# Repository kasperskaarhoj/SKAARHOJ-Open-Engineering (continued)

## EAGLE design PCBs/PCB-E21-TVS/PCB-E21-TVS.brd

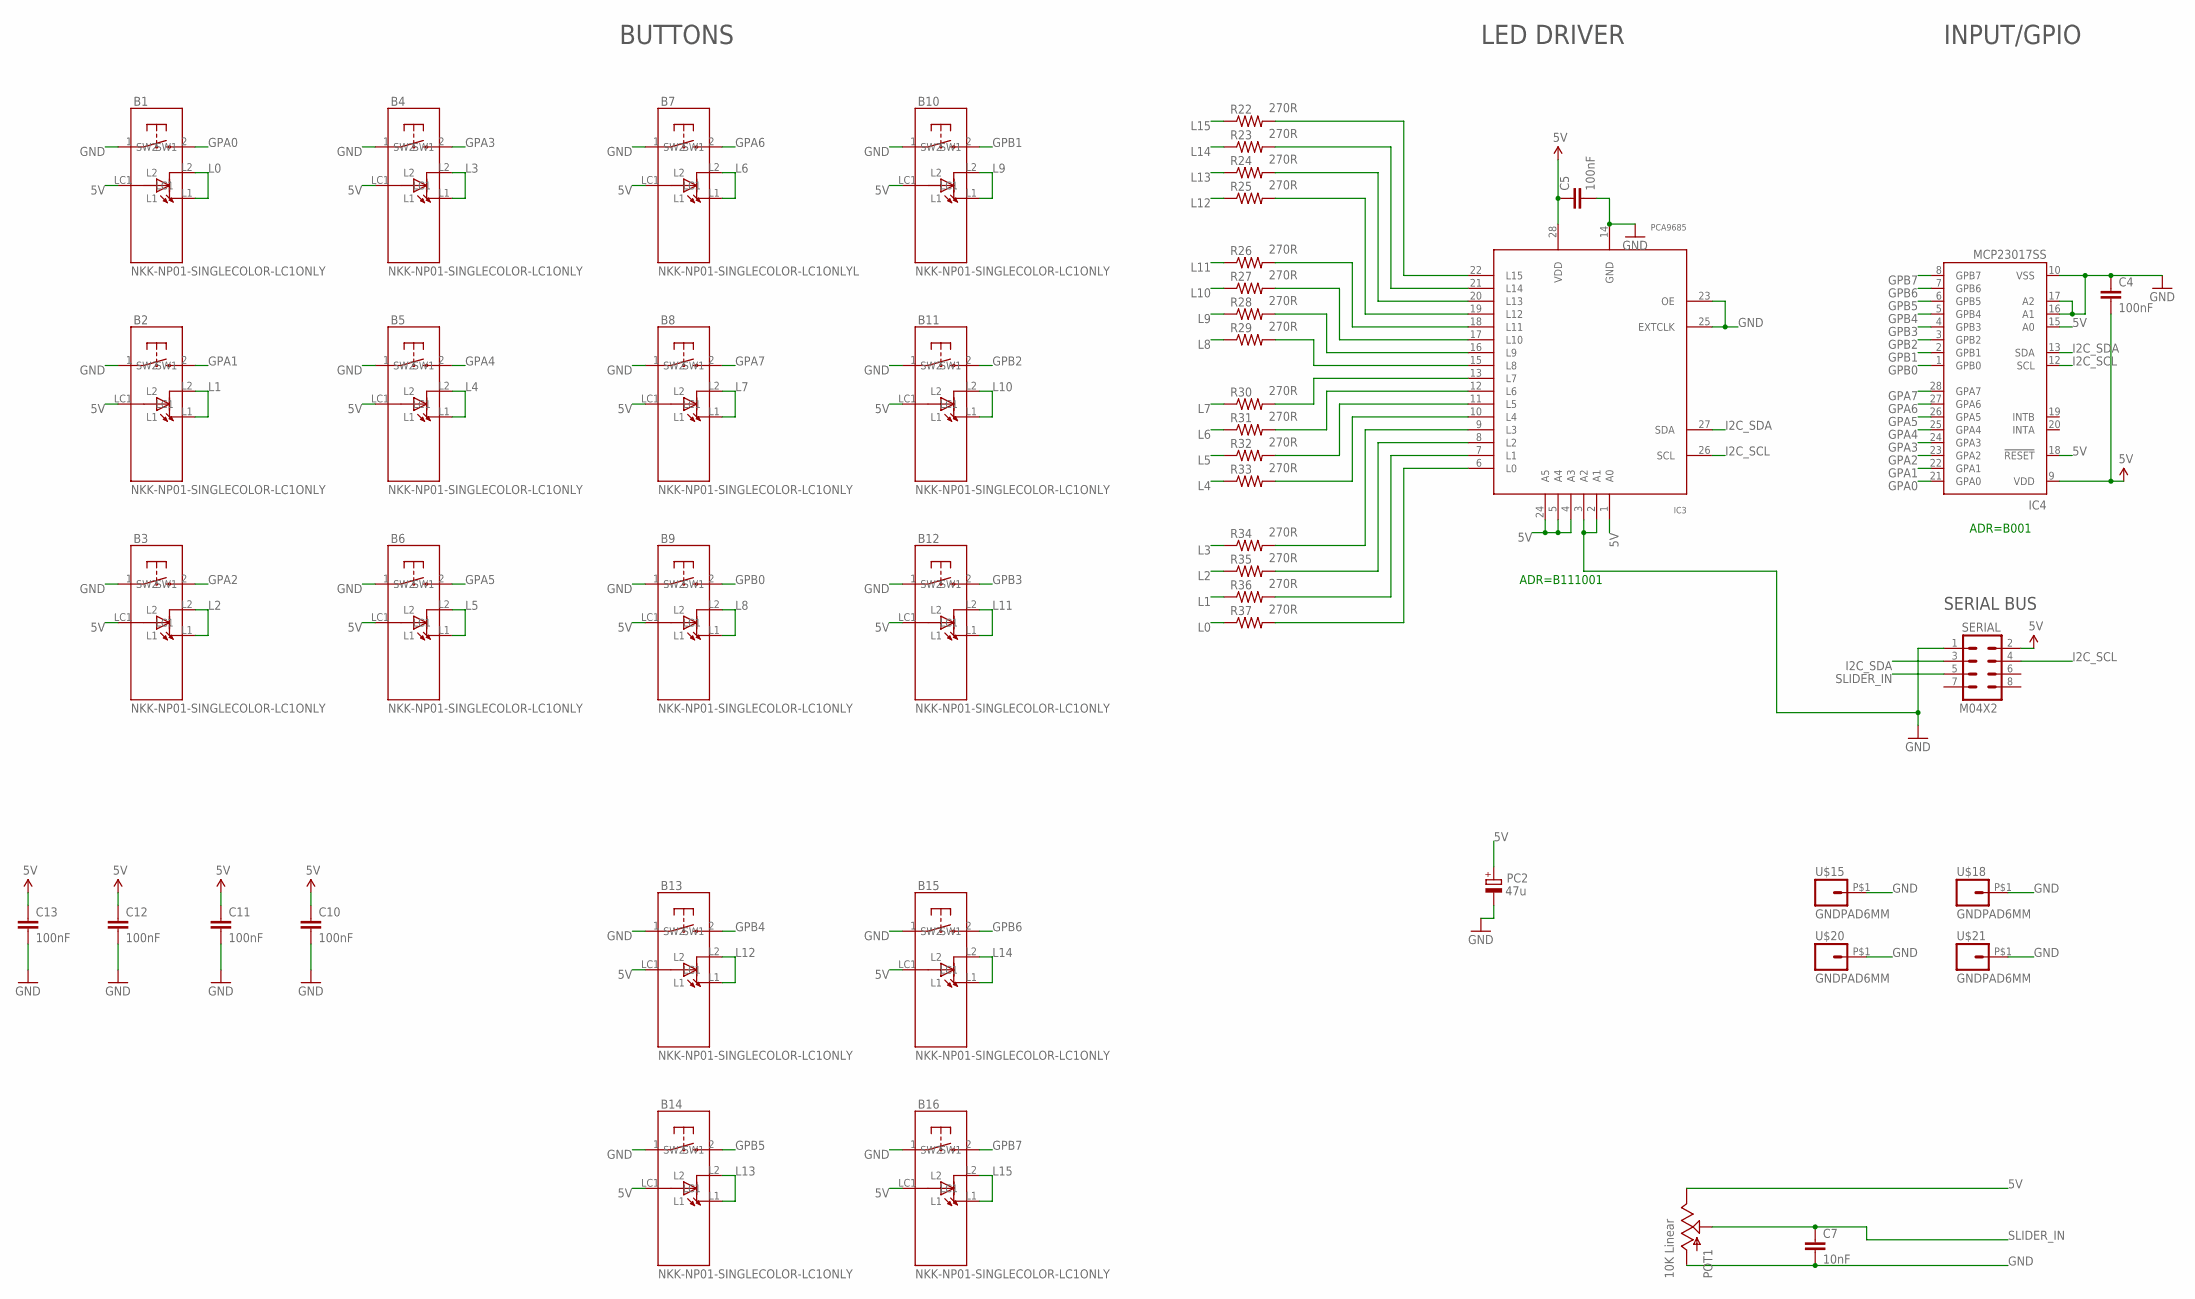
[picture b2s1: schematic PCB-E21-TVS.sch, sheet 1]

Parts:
B1, B2, B3, B4, B5, B6, B8, B9, B10, B11, B12, B13, B14, B15, B16: NKK-NP01-SINGLECOLOR-LC1ONLY; NKK-NP01_LESSHOLES2
B7: NKK-NP01-SINGLECOLOR-LC1ONLYL; NKK-NP01_LESSHOLES3
C4, C5, C10, C11, C12, C13: 100nF; 0603-CAP
C7: 10nF; 0603-CAP
IC3: PCA9685; TSSOP28
IC4: MCP23017SS; SSOP28; MPN MCP23017-E/SS
PC2: 47u; PANASONIC_D
POT1: 10K Linear; SLIDER20-CAR2
R22, R23, R24, R25, R26, R27, R28, R29, R30, R31, R32, R33, R34, R35, R36, R37: 270R; 0603-RES
SERIAL: M04X2; 2X4
U$15, U$18, U$20, U$21: GNDPAD6MM; 3.2MMPAD6MM

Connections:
5V: B1.LC1, B2.LC1, B3.LC1, B4.LC1, B5.LC1, B6.LC1, B7.LC1, B8.LC1, B9.LC1, B10.LC1, B11.LC1, B12.LC1, B13.LC1, B14.LC1, B15.LC1, B16.LC1, C4.2, C5.1, C10.1, C11.1, C12.1, C13.1, IC3.1 (A0), IC3.4 (A3), IC3.5 (A4), IC3.24 (A5), IC3.28 (VDD), IC4.9 (VDD), IC4.15 (A0), IC4.18 (!RESET), PC2.+, POT1.1 (E), SERIAL.2
GND: B1.1 (SW1), B2.1 (SW1), B3.1 (SW1), B4.1 (SW1), B5.1 (SW1), B6.1 (SW1), B7.1 (SW1), B8.1 (SW1), B9.1 (SW1), B10.1 (SW1), B11.1 (SW1), B12.1 (SW1), B13.1 (SW1), B14.1 (SW1), B15.1 (SW1), B16.1 (SW1), C4.1, C5.2, C7.2, C10.2, C11.2, C12.2, C13.2, IC3.2 (A1), IC3.3 (A2), IC3.14 (GND), IC3.23 (OE), IC3.25 (EXTCLK), IC4.10 (VSS), IC4.16 (A1), IC4.17 (A2), PC2.-, POT1.3 (A), SERIAL.1, U$15.P$1, U$18.P$1, U$20.P$1, U$21.P$1
GPA0: B1.2 (SW2), IC4.21 (GPA0)
GPA1: B2.2 (SW2), IC4.22 (GPA1)
GPA2: B3.2 (SW2), IC4.23 (GPA2)
GPA3: B4.2 (SW2), IC4.24 (GPA3)
GPA4: B5.2 (SW2), IC4.25 (GPA4)
GPA5: B6.2 (SW2), IC4.26 (GPA5)
GPA6: B7.2 (SW2), IC4.27 (GPA6)
GPA7: B8.2 (SW2), IC4.28 (GPA7)
GPB0: B9.2 (SW2), IC4.1 (GPB0)
GPB1: B10.2 (SW2), IC4.2 (GPB1)
GPB2: B11.2 (SW2), IC4.3 (GPB2)
GPB3: B12.2 (SW2), IC4.4 (GPB3)
GPB4: B13.2 (SW2), IC4.5 (GPB4)
GPB5: B14.2 (SW2), IC4.6 (GPB5)
GPB6: B15.2 (SW2), IC4.7 (GPB6)
GPB7: B16.2 (SW2), IC4.8 (GPB7)
I2C_SCL: IC3.26 (SCL), IC4.12 (SCL), SERIAL.4
I2C_SDA: IC3.27 (SDA), IC4.13 (SDA), SERIAL.3
L0: B1.L1, B1.L2, R37.1
L1: B2.L1, B2.L2, R36.1
L2: B3.L1, B3.L2, R35.1
L3: B4.L1, B4.L2, R34.1
L4: B5.L1, B5.L2, R33.1
L5: B6.L1, B6.L2, R32.1
L6: B7.L1, B7.L2, R31.1
L7: B8.L1, B8.L2, R30.1
L8: B9.L1, B9.L2, R29.1
L9: B10.L1, B10.L2, R28.1
L10: B11.L1, B11.L2, R27.1
L11: B12.L1, B12.L2, R26.1
L12: B13.L1, B13.L2, R25.1
L13: B14.L1, B14.L2, R24.1
L14: B15.L1, B15.L2, R23.1
L15: B16.L1, B16.L2, R22.1
unnamed: IC3.13 (L7), R30.2
unnamed: IC3.12 (L6), R31.2
unnamed: IC3.11 (L5), R32.2
unnamed: IC3.10 (L4), R33.2
unnamed: IC3.9 (L3), R34.2
unnamed: IC3.8 (L2), R35.2
unnamed: IC3.7 (L1), R36.2
unnamed: IC3.6 (L0), R37.2
unnamed: IC3.15 (L8), R29.2
unnamed: IC3.16 (L9), R28.2
unnamed: IC3.17 (L10), R27.2
unnamed: IC3.18 (L11), R26.2
unnamed: IC3.19 (L12), R25.2
unnamed: IC3.20 (L13), R24.2
unnamed: IC3.21 (L14), R23.2
unnamed: IC3.22 (L15), R22.2
SLIDER_IN: C7.1, POT1.2A (S), SERIAL.5

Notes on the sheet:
ADR=B111001
ADR=B001
BUTTONS
LED DRIVER
INPUT/GPIO
SERIAL BUS

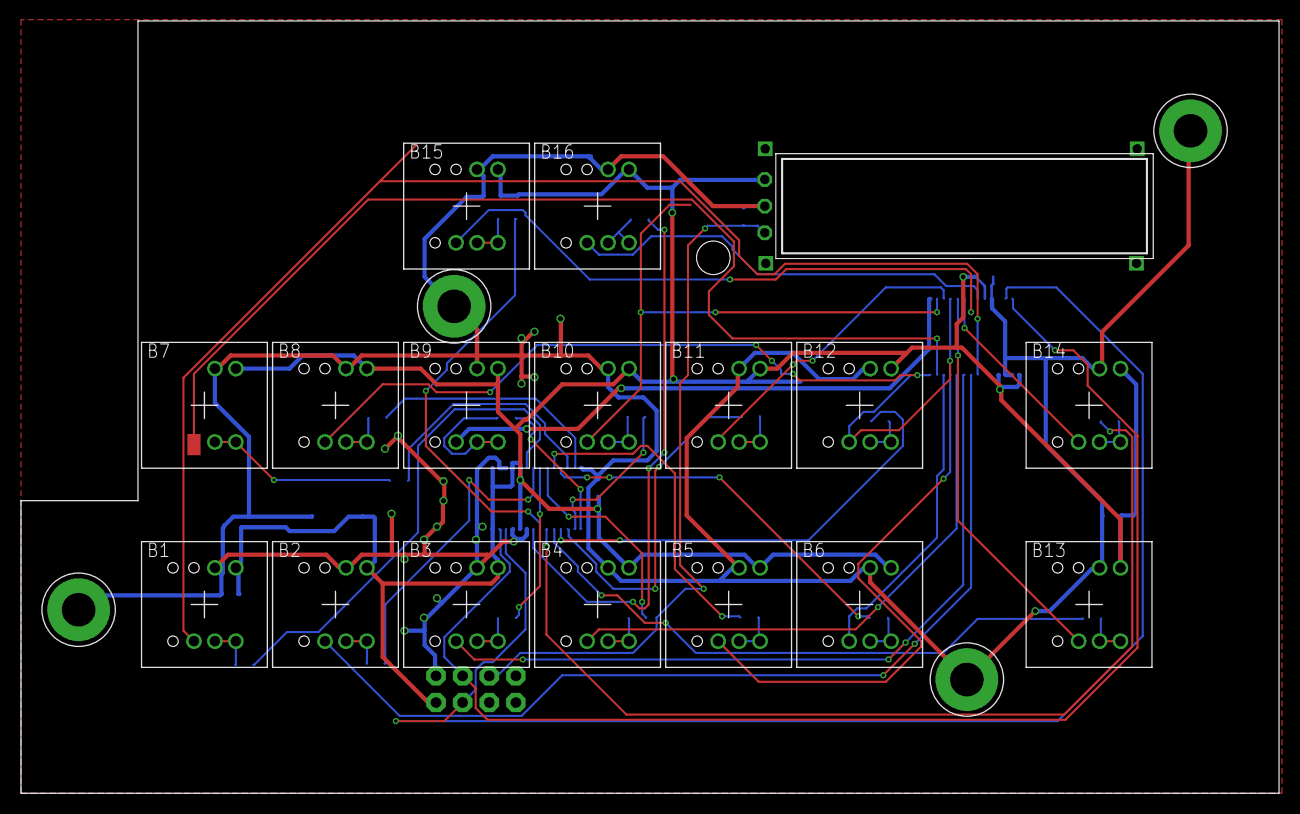
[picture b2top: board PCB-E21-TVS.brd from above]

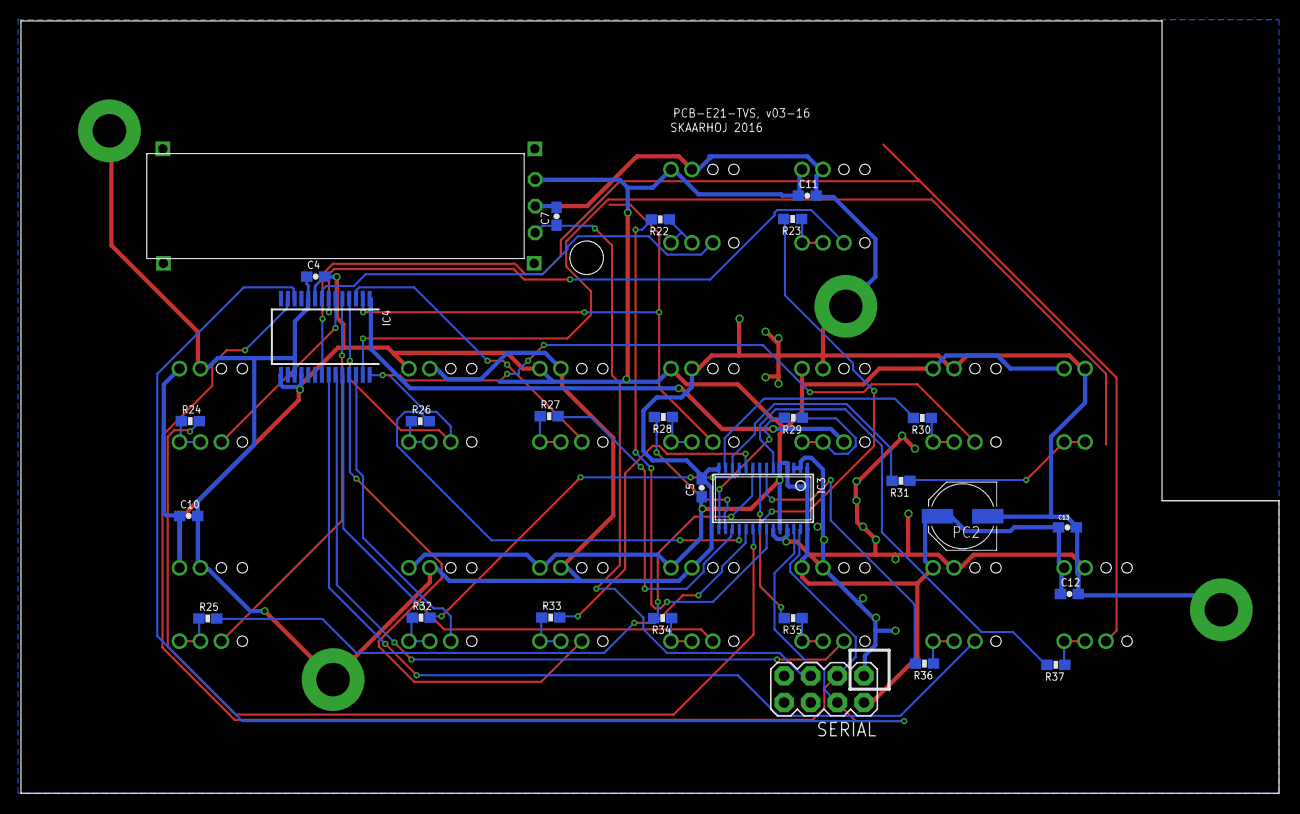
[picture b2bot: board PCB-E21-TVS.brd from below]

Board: 2 copper layers, 120.0 x 73.7 mm, 48 parts (27 on the bottom side), 53 nets.

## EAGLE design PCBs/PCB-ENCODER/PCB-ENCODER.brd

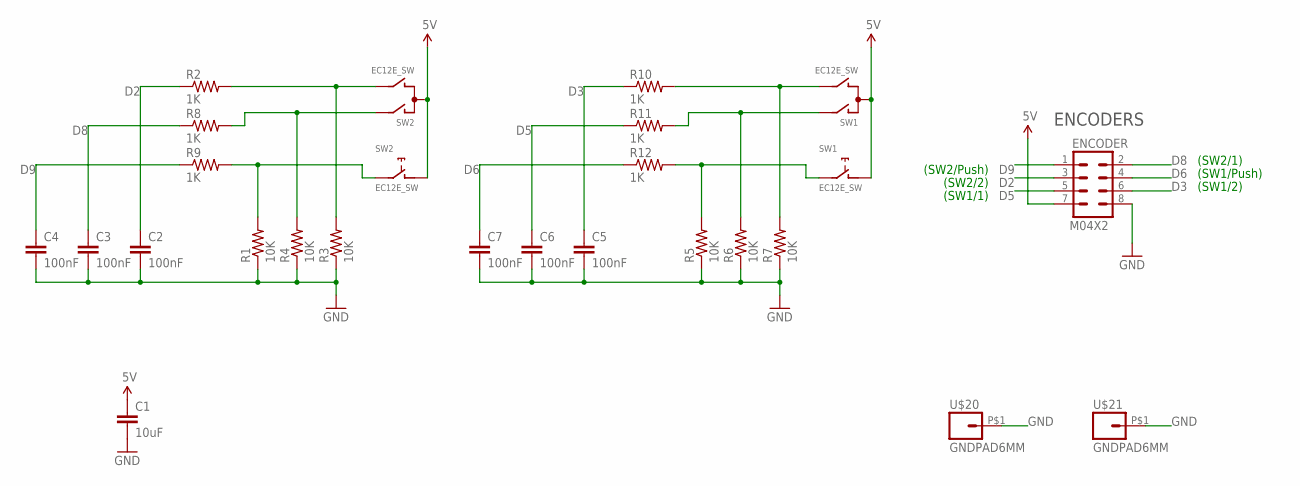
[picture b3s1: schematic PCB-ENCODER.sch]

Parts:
C1: 10uF; 0603-CAP
C2, C3, C4, C5, C6, C7: 100nF; 0603-CAP
ENCODER: M04X2; 2X4
R1, R3, R4, R5, R6, R7: 10K; 0603-RES
R2, R8, R9, R10, R11, R12: 1K; 0603-RES
SW1, SW2: EC12E_SW; ALPS_EC12E_SW
U$20, U$21: GNDPAD6MM; 3.2MMPAD6MM

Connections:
5V: C1.1, ENCODER.7, SW1.C, SW1.D (1), SW2.C, SW2.D (1)
D2: C2.1, ENCODER.3, R2.1
D3: C5.1, ENCODER.6, R10.1
D5: C6.1, ENCODER.5, R11.1
D6: C7.1, ENCODER.4, R12.1
D8: C3.1, ENCODER.2, R8.1
D9: C4.1, ENCODER.1, R9.1
GND: C1.2, C2.2, C3.2, C4.2, C5.2, C6.2, C7.2, ENCODER.8, R1.1, R3.1, R4.1, R5.1, R6.1, R7.1, U$20.P$1, U$21.P$1
unnamed: R2.2, R3.2, SW2.B
unnamed: R7.2, R10.2, SW1.B
unnamed: R6.2, R11.2, SW1.A
unnamed: R4.2, R8.2, SW2.A
unnamed: R1.2, R9.2, SW2.E (2)
unnamed: R5.2, R12.2, SW1.E (2)

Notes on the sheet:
ENCODERS
(SW2/Push)
(SW2/2)
(SW1/1)
(SW2/1)
(SW1/Push)
(SW1/2)

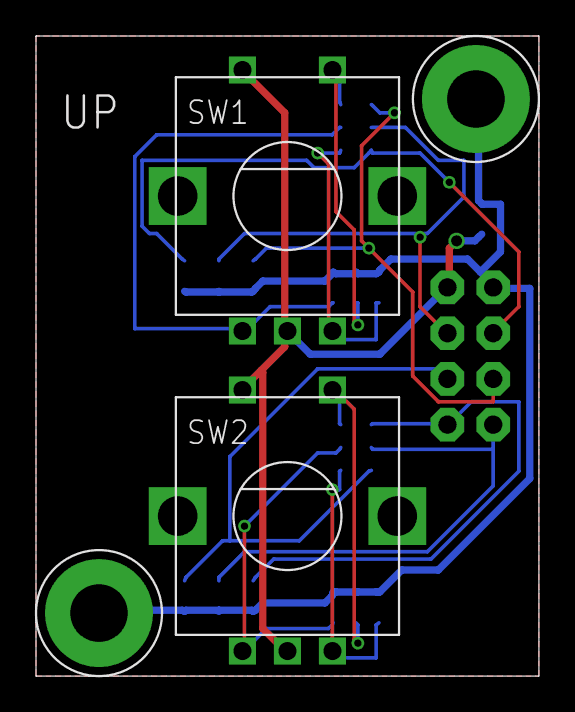
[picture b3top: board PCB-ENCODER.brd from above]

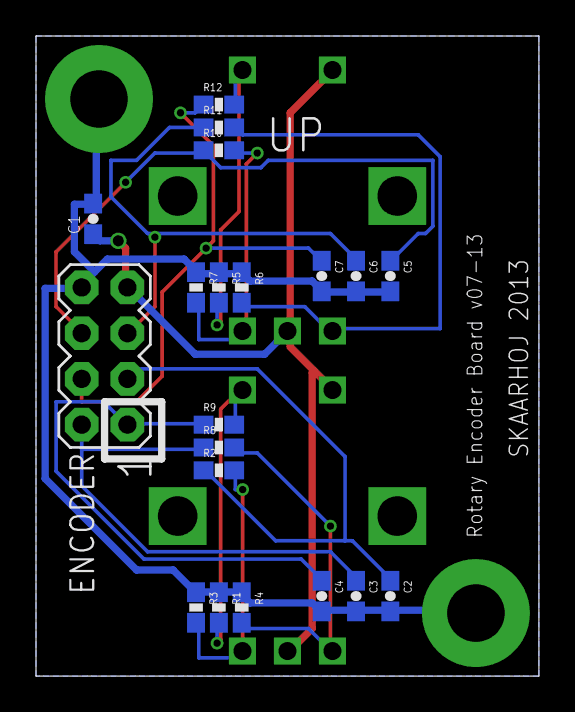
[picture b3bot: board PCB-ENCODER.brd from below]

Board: 2 copper layers, 27.9 x 35.6 mm, 24 parts (20 on the bottom side), 14 nets.

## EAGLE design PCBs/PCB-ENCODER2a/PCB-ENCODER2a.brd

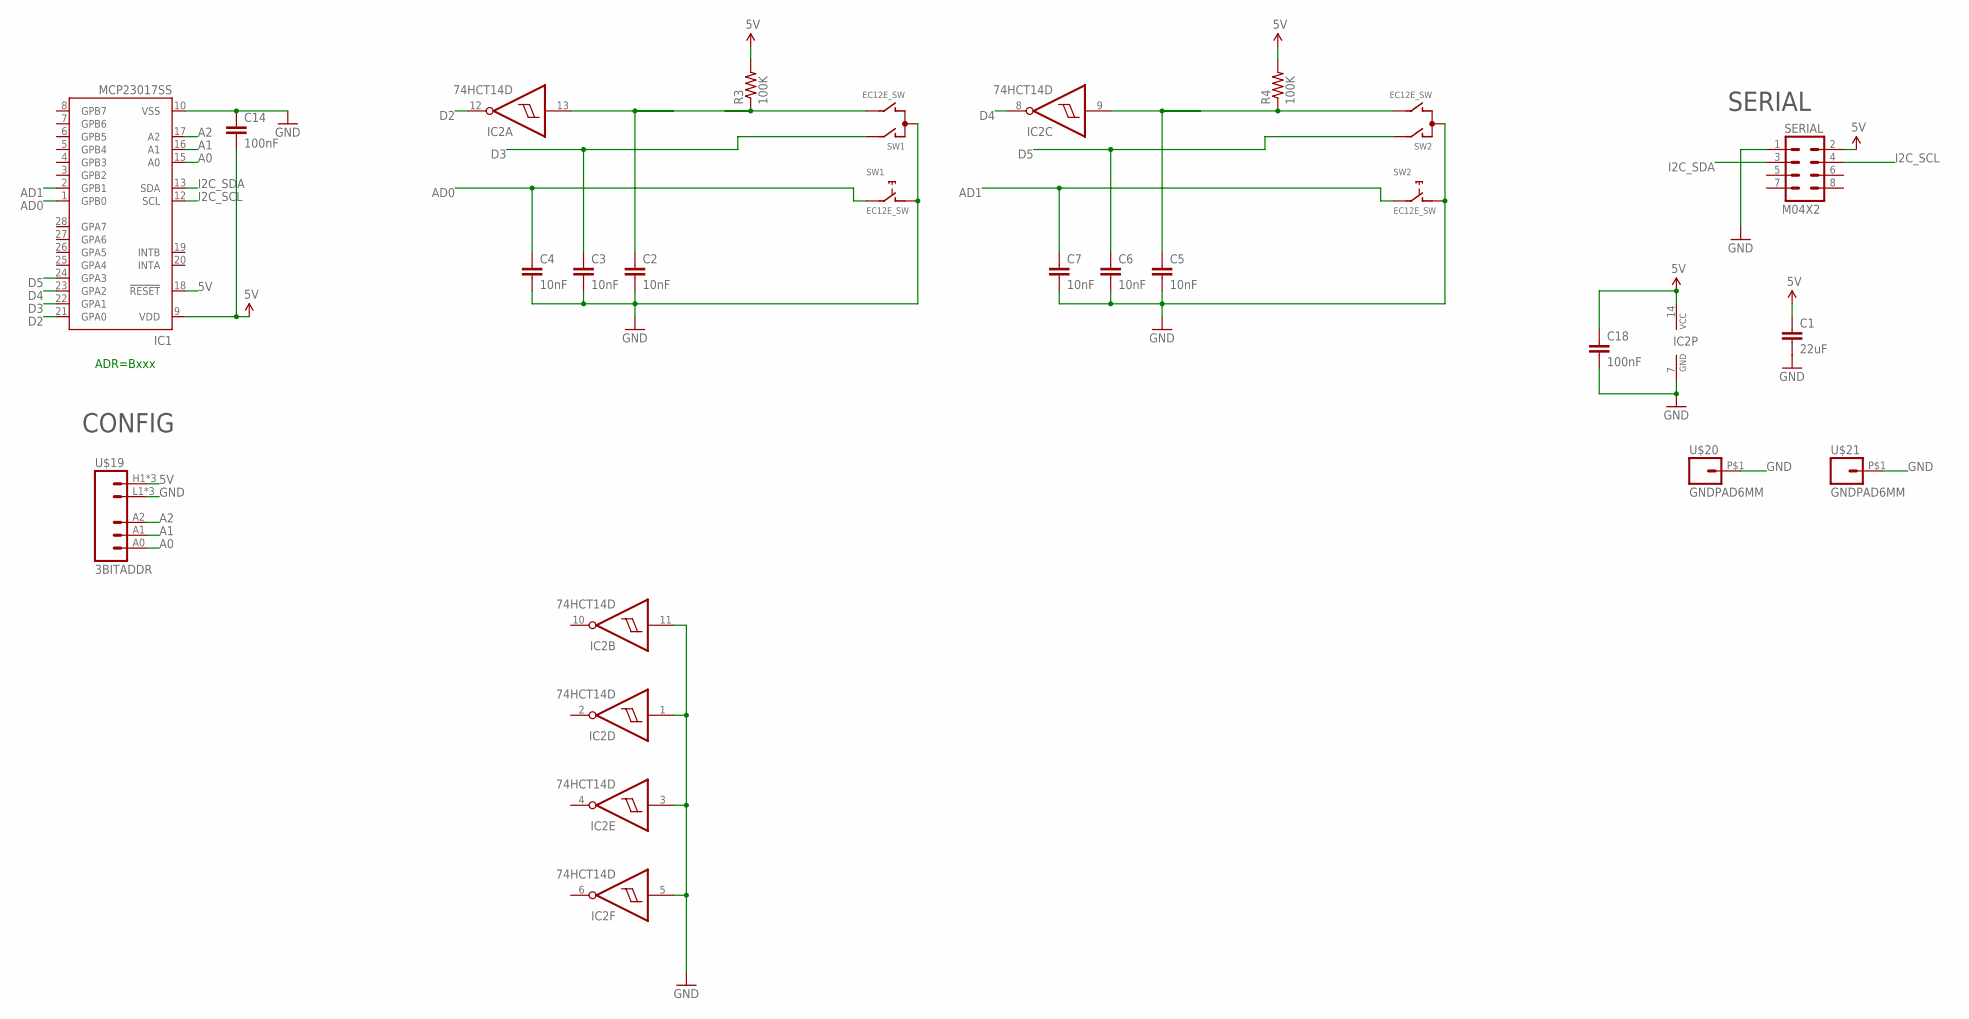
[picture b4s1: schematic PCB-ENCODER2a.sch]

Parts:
C1: 22uF; 0805
C2, C3, C4, C5, C6, C7: 10nF; 0603-CAP
C14, C18: 100nF; 0603-CAP
IC1: MCP23017SS; SSOP28; MPN MCP23017-E/SS
IC2: 74HCT14D; SO14
R3, R4: 100K; 0603-RES
SERIAL: M04X2; 2X4
SW1, SW2: EC12E_SW; ALPS_EC12E_SW
U$19: 3BITADDR
U$20, U$21: GNDPAD6MM; 3.2MMPAD6MM

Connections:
5V: C1.1, C14.2, C18.1, IC1.9 (VDD), IC1.18 (!RESET), IC2.14 (VCC), R3.2, R4.2, SERIAL.2, U$19.H1 (VCC), U$19.H2 (VCC), U$19.H3 (VCC)
A0: IC1.15 (A0), U$19.A0
A1: IC1.16 (A1), U$19.A1
A2: IC1.17 (A2), U$19.A2
AD0: C4.1, IC1.1 (GPB0), SW1.E (2)
AD1: C7.1, IC1.2 (GPB1), SW2.E (2)
D2: IC1.21 (GPA0), IC2.12 (O)
D3: C3.1, IC1.22 (GPA1), SW1.A
D4: IC1.23 (GPA2), IC2.8 (O)
D5: C6.1, IC1.24 (GPA3), SW2.A
GND: C1.2, C2.2, C3.2, C4.2, C5.2, C6.2, C7.2, C14.1, C18.2, IC1.10 (VSS), IC2.1 (I), IC2.3 (I), IC2.5 (I), IC2.7 (GND), IC2.11 (I), SERIAL.1, SW1.C, SW1.D (1), SW2.C, SW2.D (1), U$19.L1 (GND), U$19.L2 (GND), U$19.L3 (GND), U$20.P$1, U$21.P$1
I2C_SCL: IC1.12 (SCL), SERIAL.4
I2C_SDA: IC1.13 (SDA), SERIAL.3
unnamed: C2.1, IC2.13 (I), R3.1, SW1.B
unnamed: C5.1, IC2.9 (I), R4.1, SW2.B

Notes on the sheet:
SERIAL
ADR=Bxxx
CONFIG

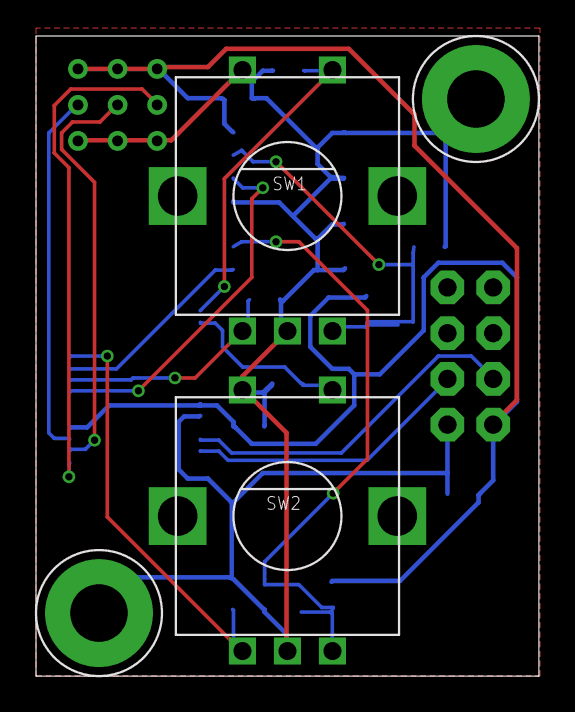
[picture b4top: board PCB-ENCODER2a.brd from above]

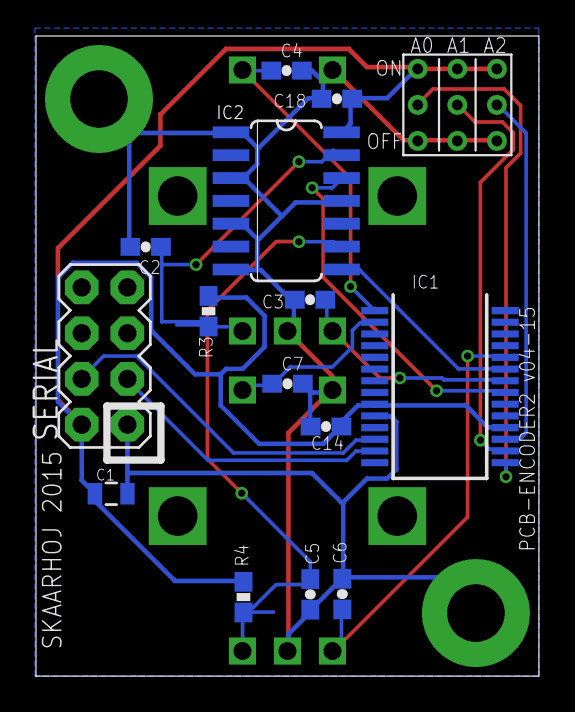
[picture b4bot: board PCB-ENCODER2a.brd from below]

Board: 2 copper layers, 27.9 x 35.6 mm, 19 parts (15 on the bottom side), 15 nets.
